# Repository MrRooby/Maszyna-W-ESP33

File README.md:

# Maszyna W - ESP32 Server

This project is a software implementation for hosting an Access Point and Web Server on ESP32 microcontroller. It features WebSocket communication, DNS Capture Portal, and LED control.

### Prerequisites

- ESP32 microcontroller
- ESP32 development environment (e.g., Arduino IDE, PlatformIO)
- Web browser for accessing the user interface

### Installation

1. Clone the repository:
    ```bash
    git clone <repository-url>
    ```
2. Set up the ESP32 development environment (PlatformIO recomended).
3. Upload the website build to the ESP32.
    ```bash
    pio run --target uploadfs
    ```
4. Upload the main script to the ESP32
    ```bash
    pio run --target upload
    ```
5. Run the program

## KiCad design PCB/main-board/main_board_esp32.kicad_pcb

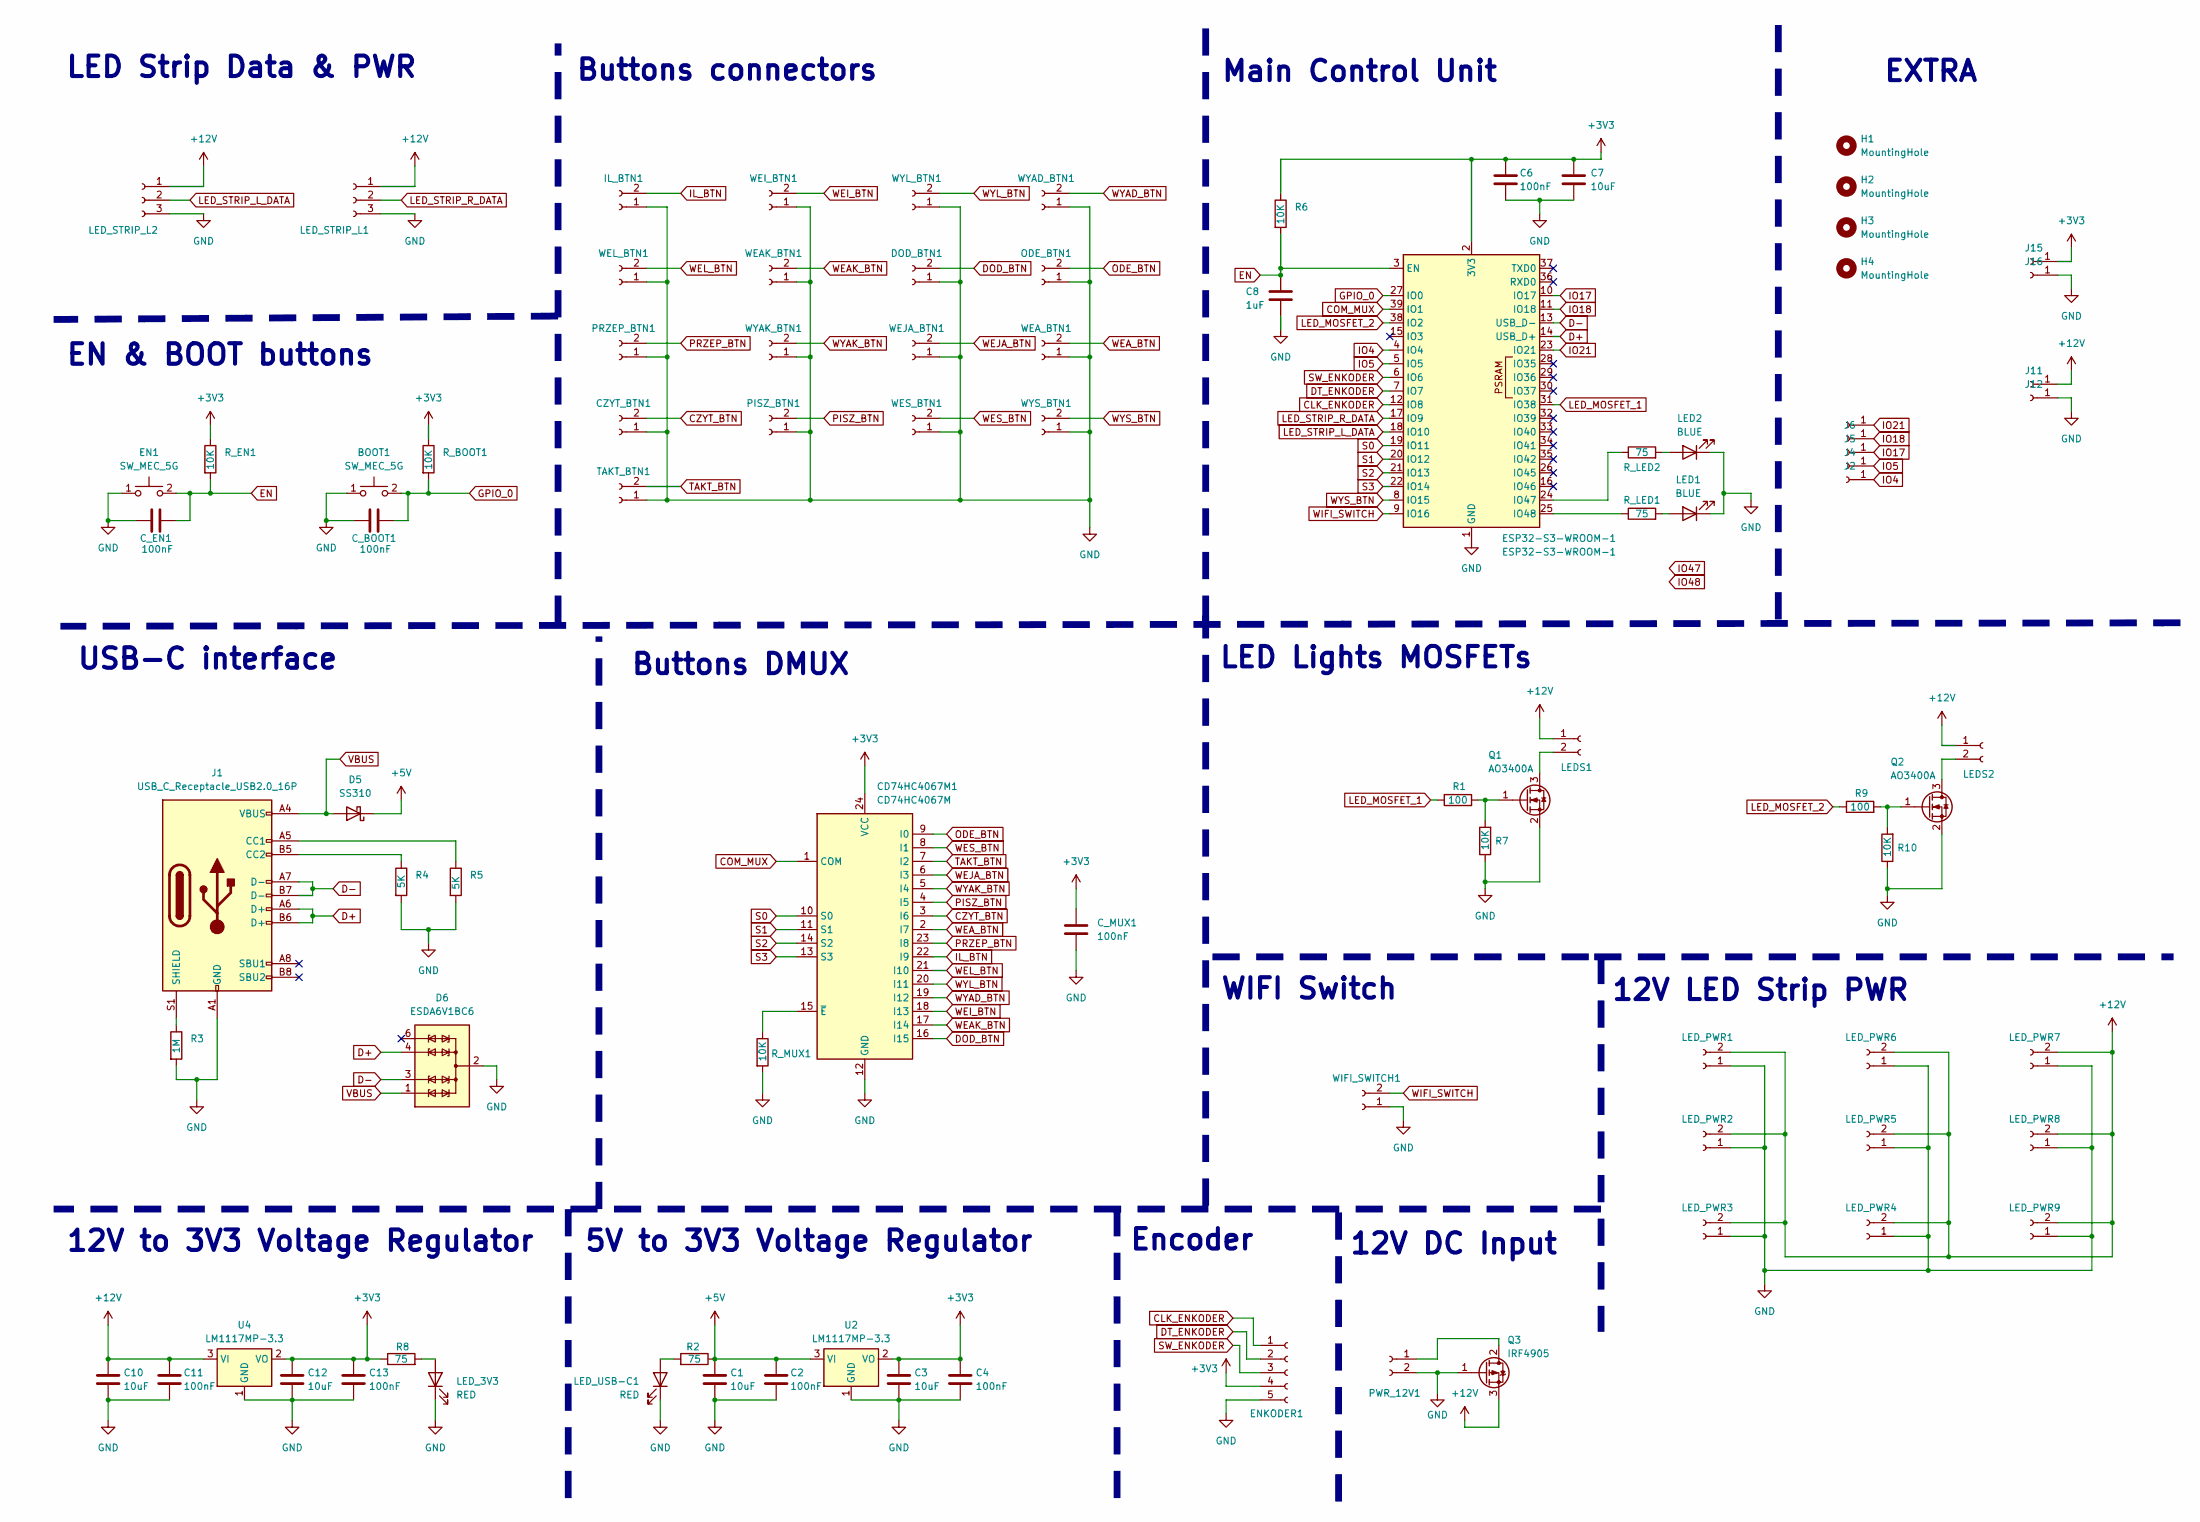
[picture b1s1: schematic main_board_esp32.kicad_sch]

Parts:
BOOT1: SW_MEC_5G; SW_Push_1P1T_NO_CK_KMR2
C1, C3, C7, C10, C12: 10uF; C_1206_3216Metric_Pad1.33x1.80mm_HandSolder
C2, C4, C6, C11, C13: 100nF; C_1206_3216Metric_Pad1.33x1.80mm_HandSolder
C8: 1uF; C_1206_3216Metric_Pad1.33x1.80mm_HandSolder
CD74HC4067M1: CD74HC4067M; SOIC-24W_7.5x15.4mm_P1.27mm
CZYT_BTN1: Conn_01x02_Socket; JST_ZH_S2B-ZR-SM4A-TF_1x02-1MP_P1.50mm_Horizontal
C_BOOT1: 100nF; C_1206_3216Metric_Pad1.33x1.80mm_HandSolder
C_EN1: 100nF; C_1206_3216Metric_Pad1.33x1.80mm_HandSolder
C_MUX1: 100nF; C_1206_3216Metric_Pad1.33x1.80mm_HandSolder
D5: SS310; D_SMA
D6: ESDA6V1BC6; SOT-23-6
DOD_BTN1: Conn_01x02_Socket; JST_ZH_S2B-ZR-SM4A-TF_1x02-1MP_P1.50mm_Horizontal
EN1: SW_MEC_5G; SW_Push_1P1T_NO_CK_KMR2
ENKODER1: Conn_01x05_Socket; JST_ZH_S5B-ZR-SM4A-TF_1x05-1MP_P1.50mm_Horizontal
ESP32-S3-WROOM-1: ESP32-S3-WROOM-1
H1, H2, H3, H4: MountingHole; MountingHole_3.2mm_M3
IL_BTN1: Conn_01x02_Socket; JST_ZH_S2B-ZR-SM4A-TF_1x02-1MP_P1.50mm_Horizontal
J1: USB_C_Receptacle_USB2.0_16P; USB_C_Receptacle_GCT_USB4085
J2, J4, J5, J6, J7, J11, J12, J15, J16: Conn_01x01_Socket; TestPoint_Pad_D2.5mm
LED1, LED2: BLUE; LED_1206_3216Metric
LEDS1, LEDS2: Conn_01x02_Socket; JST_XH_S2B-XH-A_1x02_P2.50mm_Horizontal
LED_3V3: RED; LED_1206_3216Metric
LED_PWR1, LED_PWR2, LED_PWR3, LED_PWR4, LED_PWR5, LED_PWR6, LED_PWR7, LED_PWR8, LED_PWR9: Conn_01x02_Socket; JST_XH_S2B-XH-A_1x02_P2.50mm_Horizontal
LED_STRIP_L1, LED_STRIP_L2: Conn_01x03_Socket; JST_XH_S3B-XH-A_1x03_P2.50mm_Horizontal
LED_USB-C1: RED; LED_1206_3216Metric
ODE_BTN1: Conn_01x02_Socket; JST_ZH_S2B-ZR-SM4A-TF_1x02-1MP_P1.50mm_Horizontal
PISZ_BTN1: Conn_01x02_Socket; JST_ZH_S2B-ZR-SM4A-TF_1x02-1MP_P1.50mm_Horizontal
PRZEP_BTN1: Conn_01x02_Socket; JST_ZH_S2B-ZR-SM4A-TF_1x02-1MP_P1.50mm_Horizontal
PWR_12V1: Conn_01x02_Socket; TerminalBlock_MaiXu_MX126-5.0-02P_1x02_P5.00mm
Q1, Q2: AO3400A; SOT-23
Q3: IRF4905; TO-252-2
R1, R9: 100; R_1206_3216Metric_Pad1.30x1.75mm_HandSolder
R2, R8: 75; R_1206_3216Metric_Pad1.30x1.75mm_HandSolder
R3: 1M; R_1206_3216Metric_Pad1.30x1.75mm_HandSolder
R4, R5: 5K; R_1206_3216Metric_Pad1.30x1.75mm_HandSolder
R6, R7, R10: 10K; R_1206_3216Metric_Pad1.30x1.75mm_HandSolder
R_BOOT1: 10K; R_1206_3216Metric_Pad1.30x1.75mm_HandSolder
R_EN1: 10K; R_1206_3216Metric_Pad1.30x1.75mm_HandSolder
R_LED1, R_LED2: 75; C_1206_3216Metric_Pad1.33x1.80mm_HandSolder
R_MUX1: 10K; R_1206_3216Metric_Pad1.30x1.75mm_HandSolder
TAKT_BTN1: Conn_01x02_Socket; JST_ZH_S2B-ZR-SM4A-TF_1x02-1MP_P1.50mm_Horizontal
U2, U4: LM1117MP-3.3; SOT-223-3_TabPin2
WEAK_BTN1: Conn_01x02_Socket; JST_ZH_S2B-ZR-SM4A-TF_1x02-1MP_P1.50mm_Horizontal
WEA_BTN1: Conn_01x02_Socket; JST_ZH_S2B-ZR-SM4A-TF_1x02-1MP_P1.50mm_Horizontal
WEI_BTN1: Conn_01x02_Socket; JST_ZH_S2B-ZR-SM4A-TF_1x02-1MP_P1.50mm_Horizontal
WEJA_BTN1: Conn_01x02_Socket; JST_ZH_S2B-ZR-SM4A-TF_1x02-1MP_P1.50mm_Horizontal
WEL_BTN1: Conn_01x02_Socket; JST_ZH_S2B-ZR-SM4A-TF_1x02-1MP_P1.50mm_Horizontal
WES_BTN1: Conn_01x02_Socket; JST_ZH_S2B-ZR-SM4A-TF_1x02-1MP_P1.50mm_Horizontal
WIFI_SWITCH1: Conn_01x02_Socket; JST_ZH_S2B-ZR-SM4A-TF_1x02-1MP_P1.50mm_Horizontal
WYAD_BTN1: Conn_01x02_Socket; JST_ZH_S2B-ZR-SM4A-TF_1x02-1MP_P1.50mm_Horizontal
WYAK_BTN1: Conn_01x02_Socket; JST_ZH_S2B-ZR-SM4A-TF_1x02-1MP_P1.50mm_Horizontal
WYL_BTN1: Conn_01x02_Socket; JST_ZH_S2B-ZR-SM4A-TF_1x02-1MP_P1.50mm_Horizontal
WYS_BTN1: Conn_01x02_Socket; JST_ZH_S2B-ZR-SM4A-TF_1x02-1MP_P1.50mm_Horizontal

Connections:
+3V3: C3.1, C4.1, C6.1, C7.1, C12.1, C13.1, CD74HC4067M1.24 (VCC), C_MUX1.1, ENKODER1.4, ESP32-S3-WROOM-1.2 (3V3), J15.1, R6.1, R8.1, R_BOOT1.1, R_EN1.1, U2.2 (VO), U4.2 (VO)
+5V: C1.1, C2.1, D5.1 (K), R2.1, U2.3 (VI)
+12V: C10.1, C11.1, J11.1, LEDS1.1, LEDS2.1, LED_PWR1.2, LED_PWR2.2, LED_PWR3.2, LED_PWR4.2, LED_PWR5.2, LED_PWR6.2, LED_PWR7.2, LED_PWR8.2, LED_PWR9.2, LED_STRIP_L1.1, LED_STRIP_L2.1, Q3.3 (S), U4.3 (VI)
CLK_ENKODER: ENKODER1.1, ESP32-S3-WROOM-1.12 (IO8)
COM_MUX: CD74HC4067M1.1 (COM), ESP32-S3-WROOM-1.39 (IO1)
CZYT_BTN: CD74HC4067M1.3 (I6), CZYT_BTN1.2
D+: D6.4 (TVS3), ESP32-S3-WROOM-1.14 (USB_D+), J1.A6 (D+), J1.B6 (D+)
D-: D6.3 (TVS2), ESP32-S3-WROOM-1.13 (USB_D-), J1.A7 (D-), J1.B7 (D-)
DOD_BTN: CD74HC4067M1.16 (I15), DOD_BTN1.2
DT_ENKODER: ENKODER1.2, ESP32-S3-WROOM-1.7 (IO7)
EN: C8.1, C_EN1.2, EN1.2 (B), ESP32-S3-WROOM-1.3 (EN), R6.2, R_EN1.2
GND: BOOT1.1 (A), C1.2, C2.2, C3.2, C4.2, C6.2, C7.2, C8.2, C10.2, C11.2, C12.2, C13.2, CD74HC4067M1.12 (GND), CZYT_BTN1.1, C_BOOT1.1, C_EN1.1, C_MUX1.2, D6.2 (COM), D6.5 (COM), DOD_BTN1.1, EN1.1 (A), ENKODER1.5, ESP32-S3-WROOM-1.1 (GND), ESP32-S3-WROOM-1.40 (GND), ESP32-S3-WROOM-1.41 (GND), IL_BTN1.1, J1.A1 (GND), J1.A12 (GND), J1.B1 (GND), J1.B12 (GND), J12.1, J16.1, LED1.1 (K), LED2.1 (K), LED_3V3.1 (K), LED_PWR1.1, LED_PWR2.1, LED_PWR3.1, LED_PWR4.1, LED_PWR5.1, LED_PWR6.1, LED_PWR7.1, LED_PWR8.1, LED_PWR9.1, LED_STRIP_L1.3, LED_STRIP_L2.3, LED_USB-C1.1 (K), ODE_BTN1.1, PISZ_BTN1.1, PRZEP_BTN1.1, PWR_12V1.2, Q1.2 (S), Q2.2 (S), Q3.1 (G), R3.2, R4.2, R5.2, R7.1, R10.1, R_MUX1.2, TAKT_BTN1.1, U2.1 (GND), U4.1 (GND), WEAK_BTN1.1, WEA_BTN1.1, WEI_BTN1.1, WEJA_BTN1.1, WEL_BTN1.1, WES_BTN1.1, WIFI_SWITCH1.1, WYAD_BTN1.1, WYAK_BTN1.1, WYL_BTN1.1, WYS_BTN1.1; also elsewhere on the board
GPIO_0: BOOT1.2 (B), C_BOOT1.2, ESP32-S3-WROOM-1.27 (IO0), R_BOOT1.2
IL_BTN: CD74HC4067M1.22 (I9), IL_BTN1.2
IO4: ESP32-S3-WROOM-1.4 (IO4), J2.1
IO5: ESP32-S3-WROOM-1.5 (IO5), J4.1
IO17: ESP32-S3-WROOM-1.10 (IO17), J5.1
IO18: ESP32-S3-WROOM-1.11 (IO18), J6.1
IO21: ESP32-S3-WROOM-1.23 (IO21), J7.1
LED_MOSFET_1: ESP32-S3-WROOM-1.31 (IO38), R1.1
LED_MOSFET_2: ESP32-S3-WROOM-1.38 (IO2), R9.1
LED_STRIP_L_DATA: ESP32-S3-WROOM-1.18 (IO10), LED_STRIP_L2.2
LED_STRIP_R_DATA: ESP32-S3-WROOM-1.17 (IO9), LED_STRIP_L1.2
unnamed: CD74HC4067M1.15 (~E), R_MUX1.1
unnamed: ESP32-S3-WROOM-1.24 (IO47), R_LED2.1
unnamed: ESP32-S3-WROOM-1.25 (IO48), R_LED1.1
unnamed: J1.A5 (CC1), R5.1
unnamed: J1.B5 (CC2), R4.1
unnamed: J1.S1 (SHIELD), R3.1
unnamed: LED1.2 (A), R_LED1.2
unnamed: LED2.2 (A), R_LED2.2
unnamed: LEDS1.2, Q1.3 (D)
unnamed: LEDS2.2, Q2.3 (D)
unnamed: LED_3V3.2 (A), R8.2
unnamed 34: LED_USB-C1.2 (A), R2.2; also elsewhere on the board
unnamed: PWR_12V1.1, Q3.2 (D)
unnamed: Q1.1 (G), R1.2, R7.2
unnamed: Q2.1 (G), R9.2, R10.2
ODE_BTN: CD74HC4067M1.9 (I0), ODE_BTN1.2
PISZ_BTN: CD74HC4067M1.4 (I5), PISZ_BTN1.2
PRZEP_BTN: CD74HC4067M1.23 (I8), PRZEP_BTN1.2
S0: CD74HC4067M1.10 (S0), ESP32-S3-WROOM-1.19 (IO11)
S1: CD74HC4067M1.11 (S1), ESP32-S3-WROOM-1.20 (IO12)
S2: CD74HC4067M1.14 (S2), ESP32-S3-WROOM-1.21 (IO13)
S3: CD74HC4067M1.13 (S3), ESP32-S3-WROOM-1.22 (IO14)
SW_ENKODER: ENKODER1.3, ESP32-S3-WROOM-1.6 (IO6)
TAKT_BTN: CD74HC4067M1.7 (I2), TAKT_BTN1.2
VBUS: D5.2 (A), D6.1 (TVS1), J1.A4 (VBUS), J1.A9 (VBUS), J1.B4 (VBUS), J1.B9 (VBUS)
WEAK_BTN: CD74HC4067M1.17 (I14), WEAK_BTN1.2
WEA_BTN: CD74HC4067M1.2 (I7), WEA_BTN1.2
WEI_BTN: CD74HC4067M1.18 (I13), WEI_BTN1.2
WEJA_BTN: CD74HC4067M1.6 (I3), WEJA_BTN1.2
WEL_BTN: CD74HC4067M1.21 (I10), WEL_BTN1.2
WES_BTN: CD74HC4067M1.8 (I1), WES_BTN1.2
WIFI_SWITCH: ESP32-S3-WROOM-1.9 (IO16), WIFI_SWITCH1.2
WYAD_BTN: CD74HC4067M1.19 (I12), WYAD_BTN1.2
WYAK_BTN: CD74HC4067M1.5 (I4), WYAK_BTN1.2
WYL_BTN: CD74HC4067M1.20 (I11), WYL_BTN1.2
WYS_BTN: ESP32-S3-WROOM-1.8 (IO15), WYS_BTN1.2

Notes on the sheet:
12V DC Input
LED Strip Data & PWR
12V LED Strip PWR
WIFI Switch
EXTRA
USB-C interface
12V to 3V3 Voltage Regulator
Main Control Unit
EN & BOOT buttons
LED Lights MOSFETs
5V to 3V3 Voltage Regulator
Buttons DMUX
Encoder
Buttons connectors

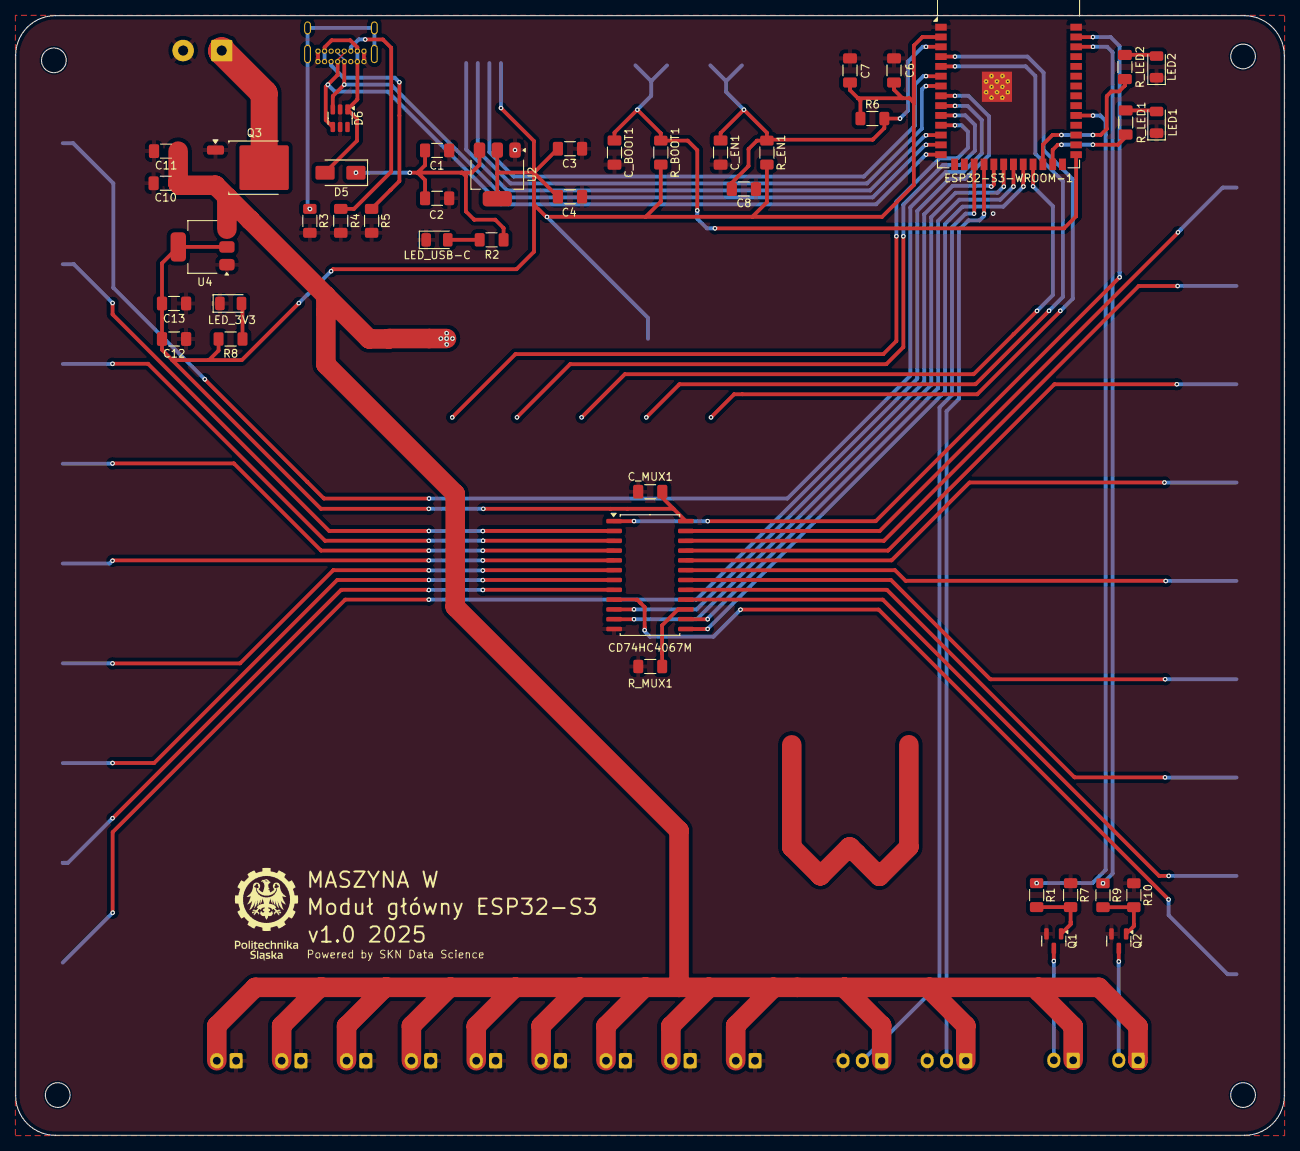
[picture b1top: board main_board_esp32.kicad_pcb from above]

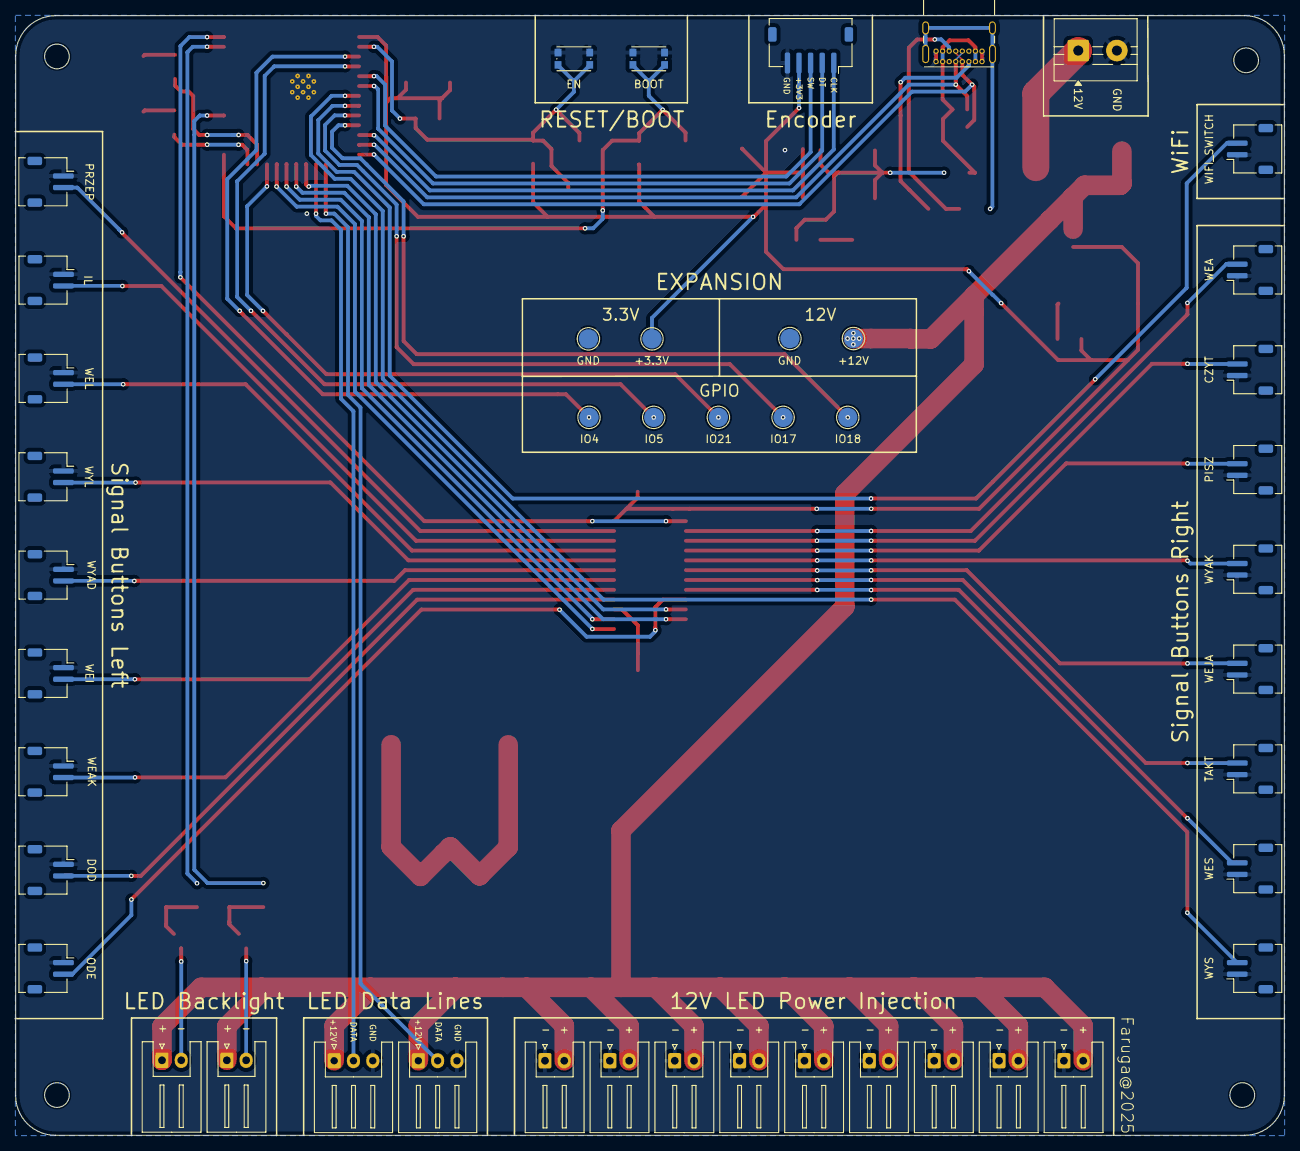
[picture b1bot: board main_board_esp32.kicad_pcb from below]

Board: 2 copper layers, 164.3 x 145.0 mm, 91 parts (45 on the bottom side), 59 nets.

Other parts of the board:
LED_USB-C: RED; LED_1206_3216Metric

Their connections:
GND: LED_USB-C.1 (K); also elsewhere on the board
unnamed 34: LED_USB-C.2 (A); also elsewhere on the board

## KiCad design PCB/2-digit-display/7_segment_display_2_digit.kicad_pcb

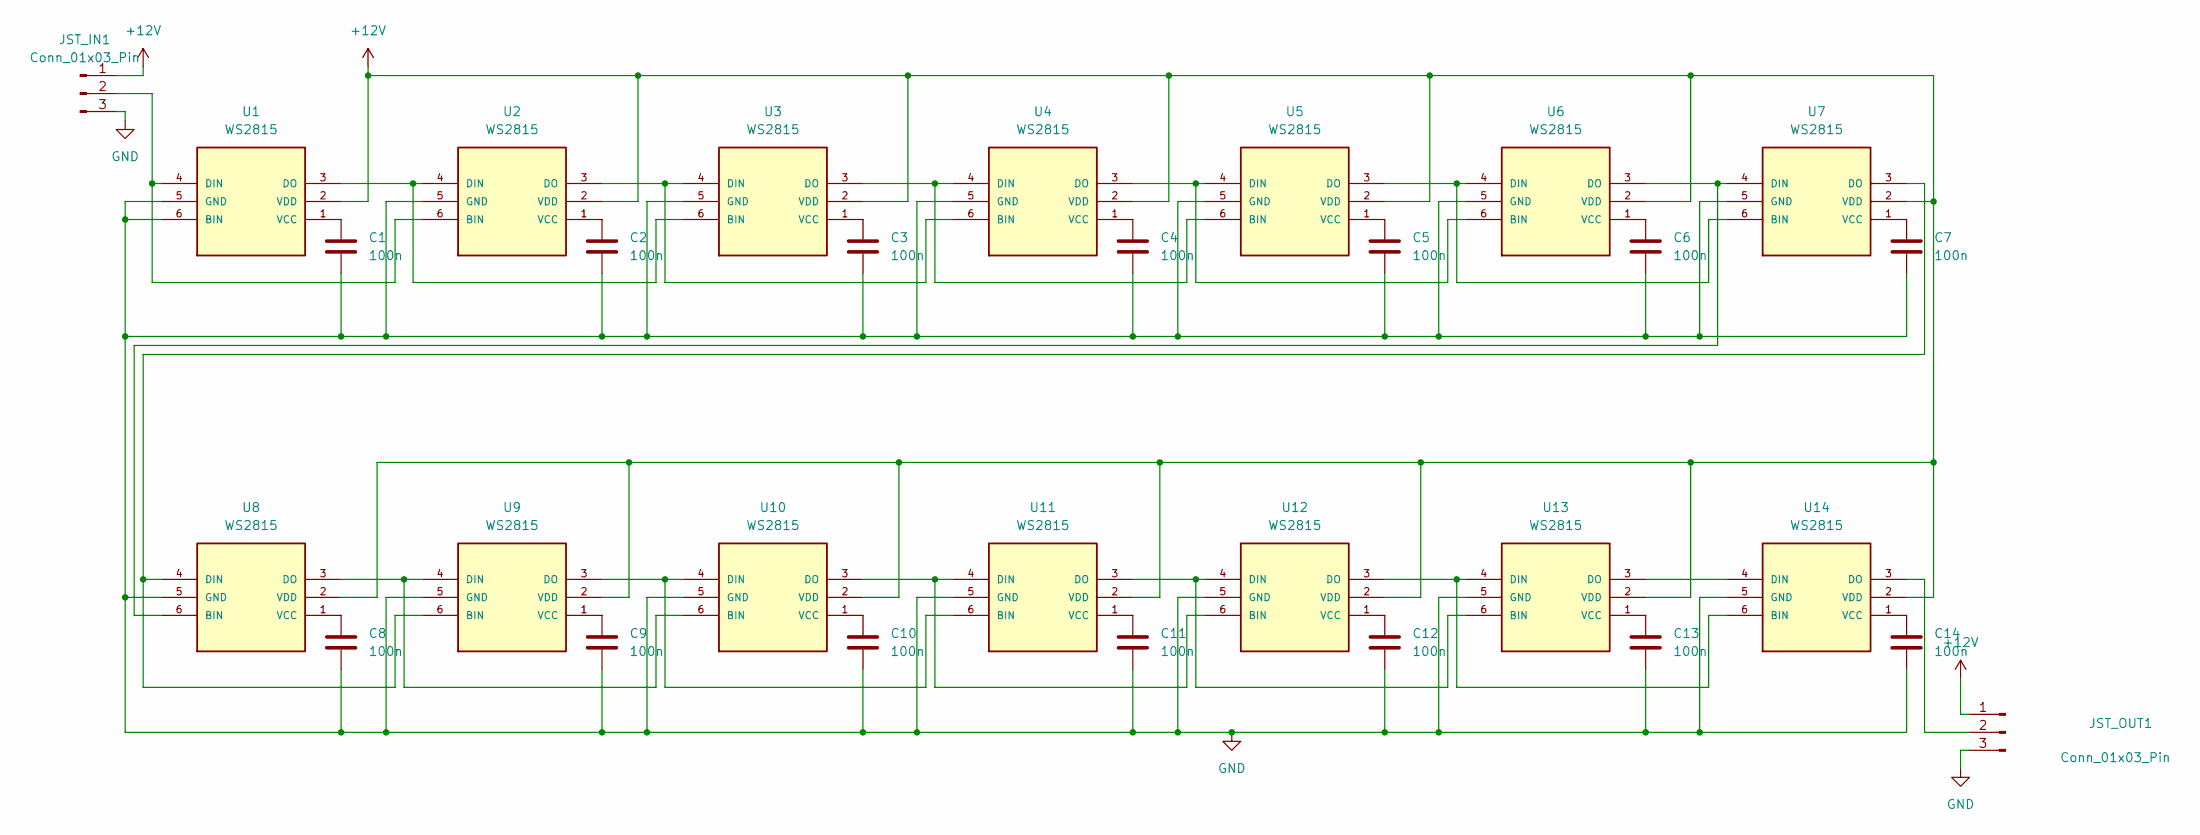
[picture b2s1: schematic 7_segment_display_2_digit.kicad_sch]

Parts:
C1, C2, C3, C4, C5, C6, C7, C8, C9, C10, C11, C12, C13, C14: 100n; C_1206_3216Metric_Pad1.33x1.80mm_HandSolder
JST_IN1: Conn_01x03_Pin; JST_XH_B3B-XH-A_1x03_P2.50mm_Vertical
JST_OUT1: Conn_01x03_Pin; JST_XH_B3B-XH-A_1x03_P2.50mm_Vertical
U1, U2, U3, U4, U5, U6, U7, U8, U9, U10, U11, U12, U13, U14: WS2815; LED-TRICOLOR-5050

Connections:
+12V: JST_IN1.1, JST_OUT1.1, U1.2 (VDD), U2.2 (VDD), U3.2 (VDD), U4.2 (VDD), U5.2 (VDD), U6.2 (VDD), U7.2 (VDD), U8.2 (VDD), U9.2 (VDD), U10.2 (VDD), U11.2 (VDD), U12.2 (VDD), U13.2 (VDD), U14.2 (VDD); also elsewhere on the board
GND: C1.2, C2.2, C3.2, C4.2, C5.2, C6.2, C7.2, C8.2, C9.2, C10.2, C11.2, C12.2, C13.2, C14.2, JST_IN1.3, JST_OUT1.3, U1.5 (GND), U1.6 (BIN), U2.5 (GND), U3.5 (GND), U4.5 (GND), U5.5 (GND), U6.5 (GND), U7.5 (GND), U8.5 (GND), U9.5 (GND), U10.5 (GND), U11.5 (GND), U12.5 (GND), U13.5 (GND), U14.5 (GND); also elsewhere on the board
unnamed 2: JST_IN1.2, U1.4 (DIN), U2.6 (BIN); also elsewhere on the board
unnamed 3: JST_OUT1.2, U14.3 (DO); also elsewhere on the board
unnamed: U1.3 (DO), U2.4 (DIN), U3.6 (BIN)
unnamed: C1.1, U1.1 (VCC)
unnamed: U2.3 (DO), U3.4 (DIN), U4.6 (BIN)
unnamed: C2.1, U2.1 (VCC)
unnamed: U3.3 (DO), U4.4 (DIN), U5.6 (BIN)
unnamed: C3.1, U3.1 (VCC)
unnamed: U4.3 (DO), U5.4 (DIN), U6.6 (BIN)
unnamed: C4.1, U4.1 (VCC)
unnamed: U5.3 (DO), U6.4 (DIN), U7.6 (BIN)
unnamed: C5.1, U5.1 (VCC)
unnamed: U6.3 (DO), U7.4 (DIN), U8.6 (BIN)
unnamed: C6.1, U6.1 (VCC)
unnamed: U7.3 (DO), U8.4 (DIN), U9.6 (BIN)
unnamed: C7.1, U7.1 (VCC)
unnamed: C8.1, U8.1 (VCC)
unnamed: C9.1, U9.1 (VCC)
unnamed: U8.3 (DO), U9.4 (DIN), U10.6 (BIN)
unnamed: U9.3 (DO), U10.4 (DIN), U11.6 (BIN)
unnamed: U10.3 (DO), U11.4 (DIN), U12.6 (BIN)
unnamed: C10.1, U10.1 (VCC)
unnamed: U11.3 (DO), U12.4 (DIN), U13.6 (BIN)
unnamed: C11.1, U11.1 (VCC)
unnamed: U12.3 (DO), U13.4 (DIN), U14.6 (BIN)
unnamed: C12.1, U12.1 (VCC)
unnamed: U13.3 (DO), U14.4 (DIN)
unnamed: C13.1, U13.1 (VCC)
unnamed: C14.1, U14.1 (VCC)

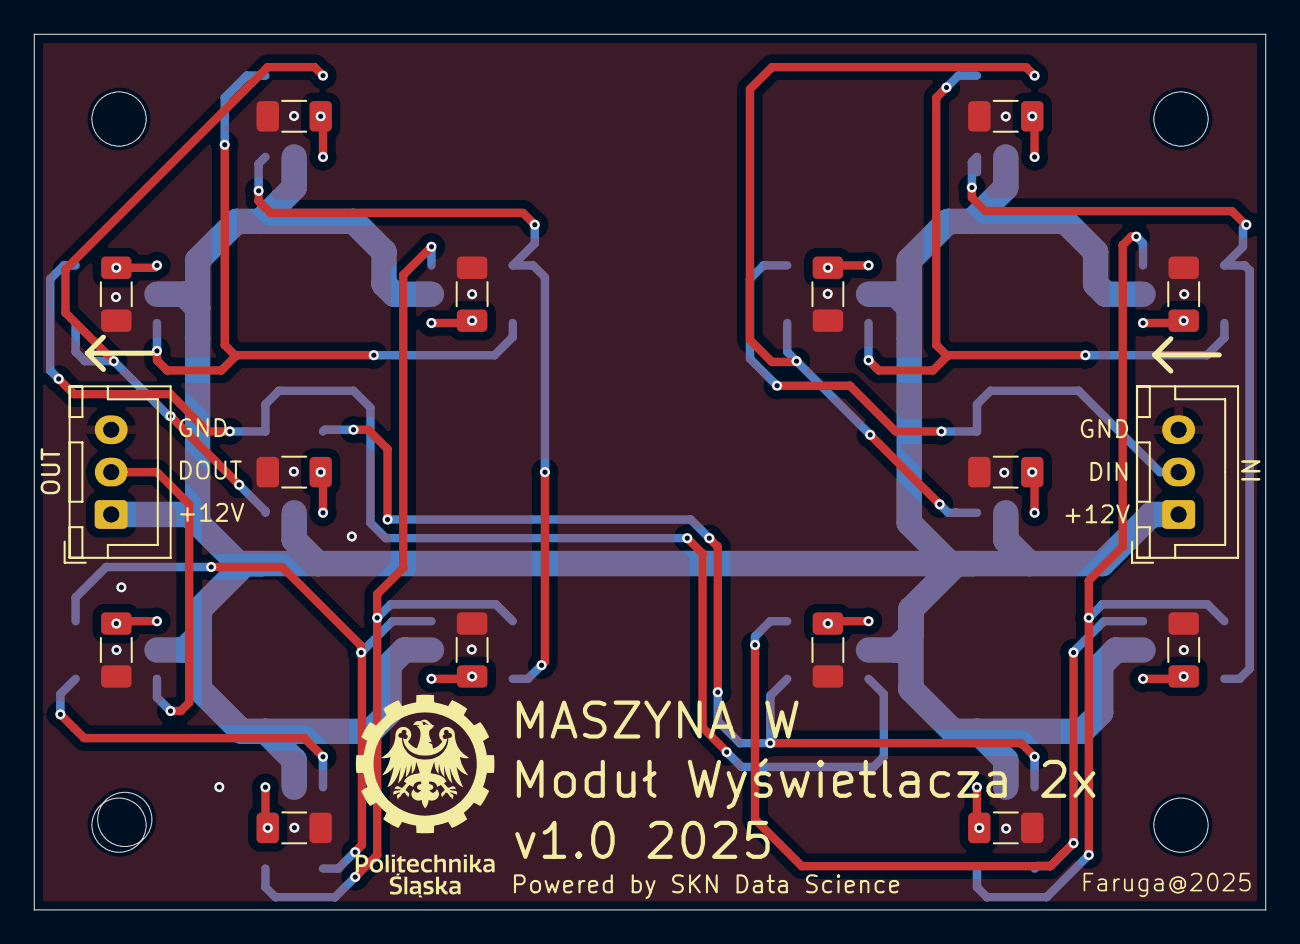
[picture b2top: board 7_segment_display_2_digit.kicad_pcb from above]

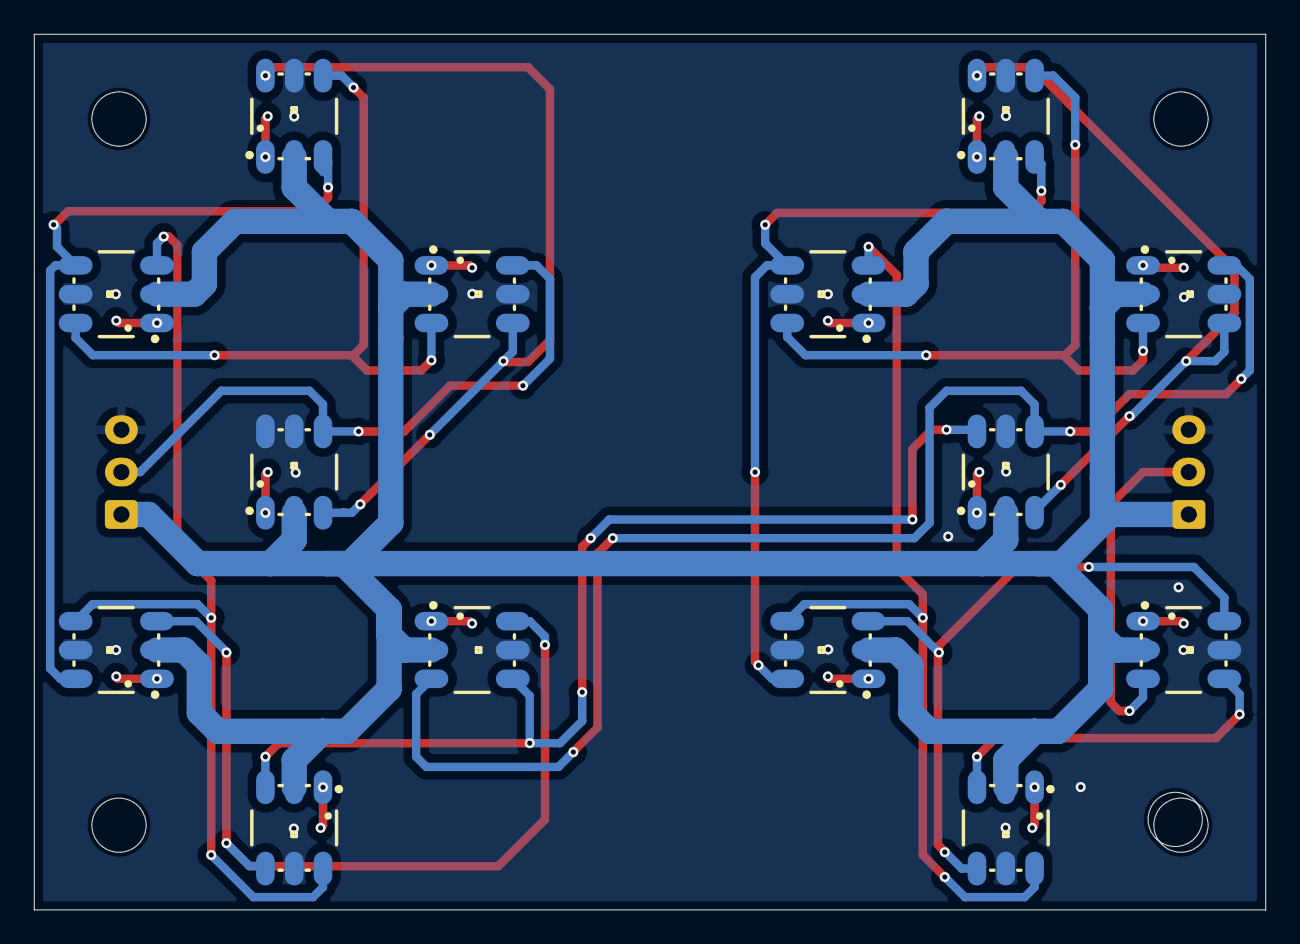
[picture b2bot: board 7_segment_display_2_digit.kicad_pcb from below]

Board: 2 copper layers, 72.7 x 51.7 mm, 30 parts (14 on the bottom side), 31 nets.

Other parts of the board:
IN: Conn_01x03_Pin; JST_XH_B3B-XH-A_1x03_P2.50mm_Vertical
OUT: Conn_01x03_Pin; JST_XH_B3B-XH-A_1x03_P2.50mm_Vertical

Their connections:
+12V: IN.1, OUT.1; also elsewhere on the board
GND: IN.3, OUT.3; also elsewhere on the board
unnamed 2: IN.2; also elsewhere on the board
unnamed 3: OUT.2; also elsewhere on the board

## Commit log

2025-03-04 added doxygen comments
2025-03-07 Working server. Hosting Vue app on ESP32 + Working WebSockets.
2025-03-25 Web Sockets working as intended client->server
2025-03-25 three segment display working with websockets. Havent tested multiple led strips.
2025-03-27 All led functions finished and working as intended
2025-03-27 Added Doxygen comments. DNSServer for a captive portal implemented and working. Changed names of num_segment_displays to num_digit_displays for better readibility
2025-03-27 Add README.md with project overview, prerequisites, and installation instructions
2025-03-28 Corection of websocket data, New build of website
2025-04-08 for testing
2025-05-04 Fixed displayManager initialization in w_Server. PaO working as intended
2025-05-19 Button implementation with debounce.
2025-05-19 websockets sending button info implemented
2025-05-24 commit for safety
2025-05-24 capacitive touch implementation
2025-06-05 New website build, updated websocket handling for both ways. All working as intended
2025-06-17 First hardware test. All displays, no buttons, no encoder.
2025-06-17 misspelling
2025-06-17 deleted redundant code
2025-06-17 fixed minor issues
2025-06-17 minor changes
2025-06-17 Implementation of NeoPixelBus Library
2025-06-18 added multiple channel support for multiple led strips
2025-06-18 added stop signal support
2025-06-18 New website build. Added stop signal implementation
2025-06-21 Updated doxygen documentation
2025-09-07 Added mux implementation, mosfet control for led backlight, changed board used for esp32 s3, continuing development of version 1.0
2025-09-12 added pcb files
2025-09-14 implemented web/local mode switching and continuing work on local machine mode
2025-09-14 mode switching functional, added buttons and partial encoder support to local machine
2025-09-15 added blinking animation for display elements
2025-09-15 encoder implementation finished
2025-10-15 added led and button tests for hardware evaluation. Captive portal not functional
2025-10-15 working captive portal, tested on pc, samsung android phone
2025-10-15 improved led testing functions
2025-10-16 encoder implementation ready for testing
2025-10-25 Add FileSystem class for managing color configurations
    - Implemented FileSystem class with methods for mounting, unmounting, and checking file existence.
    - Added functionality to save and load color configurations for display elements using LittleFS and ArduinoJson.
    - Created methods to save all colors and load all colors from a JSON configuration file.
    - Introduced helper function to map DisplayElement enum to corresponding JSON keys.
2025-11-06 Full doxygen documentation, dipslaying ip address on PaO before website accessed
2025-11-06 Captive portal fixed, changed IP address
2025-11-13 changed values of led elements for correct display positions
2025-12-04 Add display letter functionality to PAO and segment displays, modified displaying values with ability to not display leading 0.
2025-12-04 fixed button assignment, and logic
2025-12-04 added 1.5s delay for turning off BUS lines in W_Local mode, changed encoder and insert mode implementation
2025-12-05 bus lines light up for 0.7s works as intended. Working on encoder fix
2025-12-05 fixed encoder button debounce
2025-12-18 poprawy architektury symulatora
2025-12-19 nowa architektura w_local, gotowa do testow
2025-12-19 podświetlanie aktualnej linii pao, gotowe do testow
2025-12-19 wgrano nowy build strony
2025-12-19 naprawiono insert mode, poprawiono zamienione miejscami wyl<->wel i wys<->wes
2025-12-19 różne kolory dla pao, scrollowanie pao naprawione
2025-12-19 fixed encoder implementation with interrupts
2026-01-20 Add MIT License to the project
